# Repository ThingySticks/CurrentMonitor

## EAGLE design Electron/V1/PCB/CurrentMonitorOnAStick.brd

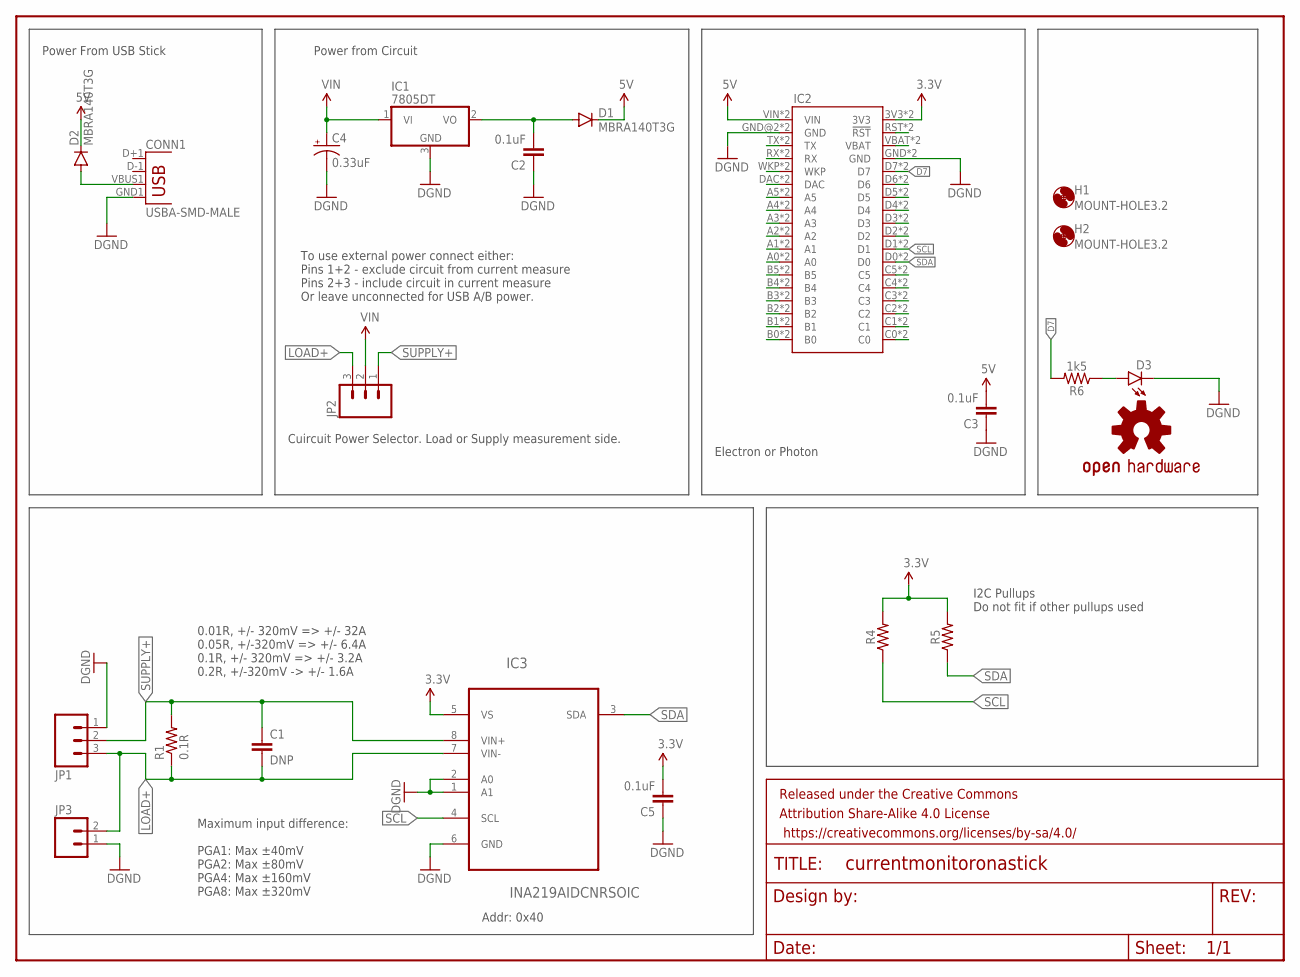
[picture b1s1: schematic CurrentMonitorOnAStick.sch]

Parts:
C1: DNP; 0805
C2, C3, C5: 0.1uF; 0805
C4: 0.33uF; EIA3216
CONN1: USBA-SMD-MALE; USB-A-SMT-MALE
D1, D2: MBRA140T3G; SMA-DIODE
D3: LED1206-BOTTOM; LED-1206-BOTTOM
FRAME2: FRAME-LETTER; CREATIVE_COMMONS
H1, H2: MOUNT-HOLE3.2; 3,2
IC1: 7805DT; TO252
IC2: ELECTRONDUALNAMED; ELECTRON_SIMPLE_SILK_NAMES_DUAL
IC3: INA219AIDCNRSOIC; SO08
JP1: M03-SCREW-5MM; SCREWTERMINAL-5MM-3
JP2: M03PTH; 1X03
JP3: M025MM; SCREWTERMINAL-5MM-2
LOGO1: OSHW-LOGOM; OSHW-LOGO-M
R1: 0.1R; 2512
R4, R5: 0805
R6: 1k5; 0805

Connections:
3.3V: C5.2, IC2.3V3, IC2.3V3_1 (3V3), IC3.5 (VS), R4.2, R5.2
5V: C3.2, D1.C, D2.C, IC2.VIN, IC2.VIN_1B (VIN)
D7: IC2.D7, IC2.D7_1 (D7), R6.2
GND: C2.1, C3.1, C4.C (-), C5.1, CONN1.GND1 (GND), D3.C, IC1.3 (GND), IC2.GND, IC2.GND@2 (GND), IC2.GND_1 (GND), IC2.GND_1B (GND), IC3.1 (A1), IC3.2 (A0), IC3.6 (GND), JP1.1, JP3.1
LOAD+: C1.2, IC3.7 (VIN-), JP1.3, JP2.3, JP3.2, R1.1
unnamed: CONN1.VBUS1 (VBUS), D2.A
unnamed: C2.2, D1.A, IC1.2 (VO)
unnamed: IC2.VBAT, IC2.VBATT_1 (VBAT)
unnamed: IC2.RST (!RST), IC2.RST_1 (!RST)
unnamed: D3.A, R6.1
unnamed: IC2.D6, IC2.D6_1 (D6)
unnamed: IC2.D5, IC2.D5_1 (D5)
unnamed: IC2.D4, IC2.D4_1 (D4)
unnamed: IC2.D3, IC2.D3_1 (D3)
unnamed: IC2.D2, IC2.D2_1 (D2)
unnamed: IC2.C5, IC2.C5_1 (C5)
unnamed: IC2.C4, IC2.C4_1 (C4)
unnamed: IC2.C3, IC2.C3_1 (C3)
unnamed: IC2.C2, IC2.C2_1 (C2)
unnamed: IC2.C1, IC2.C1_1 (C1)
unnamed: IC2.C0, IC2.C0_1 (C0)
unnamed: IC2.B0, IC2.B0_1 (B0)
unnamed: IC2.B1, IC2.B1_1 (B1)
unnamed: IC2.B2, IC2.B2_1 (B2)
unnamed: IC2.B3, IC2.B3_1 (B3)
unnamed: IC2.B4, IC2.B4_1 (B4)
unnamed: IC2.B5, IC2.B5_1 (B5)
unnamed: IC2.A0, IC2.A0_1 (A0)
unnamed: IC2.A1, IC2.A1_1 (A1)
unnamed: IC2.A2, IC2.A2_1 (A2)
unnamed: IC2.A3, IC2.A3_1 (A3)
unnamed: IC2.A4, IC2.A4_1 (A4)
unnamed: IC2.A5, IC2.A5_1 (A5)
unnamed: IC2.DAC, IC2.DAC_1 (DAC)
unnamed: IC2.WKP, IC2.WKP_1 (WKP)
unnamed: IC2.RX, IC2.RX_1 (RX)
unnamed: IC2.TX, IC2.TX_1 (TX)
SCL: IC2.D1, IC2.D1_1 (D1), IC3.4 (SCL), R4.1
SDA: IC2.D0, IC2.D0_1 (D0), IC3.3 (SDA), R5.1
SUPPLY+: C1.1, IC3.8 (VIN+), JP1.2, JP2.1, R1.2
VIN: C4.A (+), IC1.1 (VI), JP2.2

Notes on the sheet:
To use external power connect either: Pins 1+2 - exclude circuit from current measure Pins 2+3 - include circuit in current measure Or leave unconnected for USB A/B power.
I2C Pullups Do not fit if other pullups used
Maximum input difference: PGA1: Max ±40mV PGA2: Max ±80mV PGA4: Max ±160mV PGA8: Max ±320mV
0.01R, +/- 320mV => +/- 32A 0.05R, +/-320mV => +/- 6.4A 0.1R, +/- 320mV => +/- 3.2A 0.2R, +/-320mV -> +/- 1.6A
Power from Circuit
Power From USB Stick
Cuircuit Power Selector. Load or Supply measurement side.
Electron or Photon
Addr: 0x40

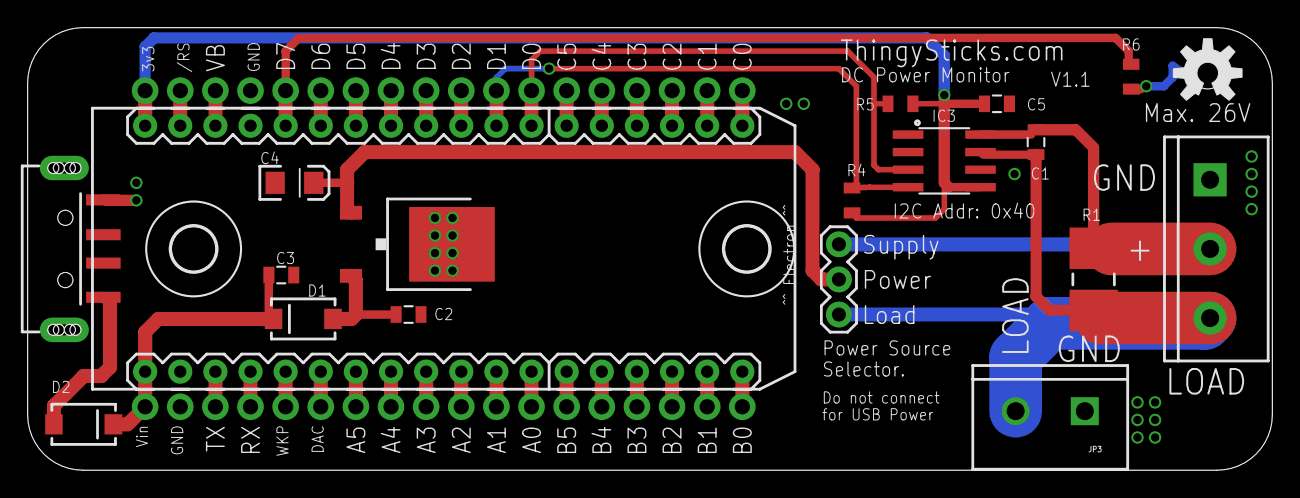
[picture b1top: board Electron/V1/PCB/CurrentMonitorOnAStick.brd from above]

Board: 2 copper layers, 90.0 x 32.0 mm, 23 parts (1 on the bottom side), 41 nets.

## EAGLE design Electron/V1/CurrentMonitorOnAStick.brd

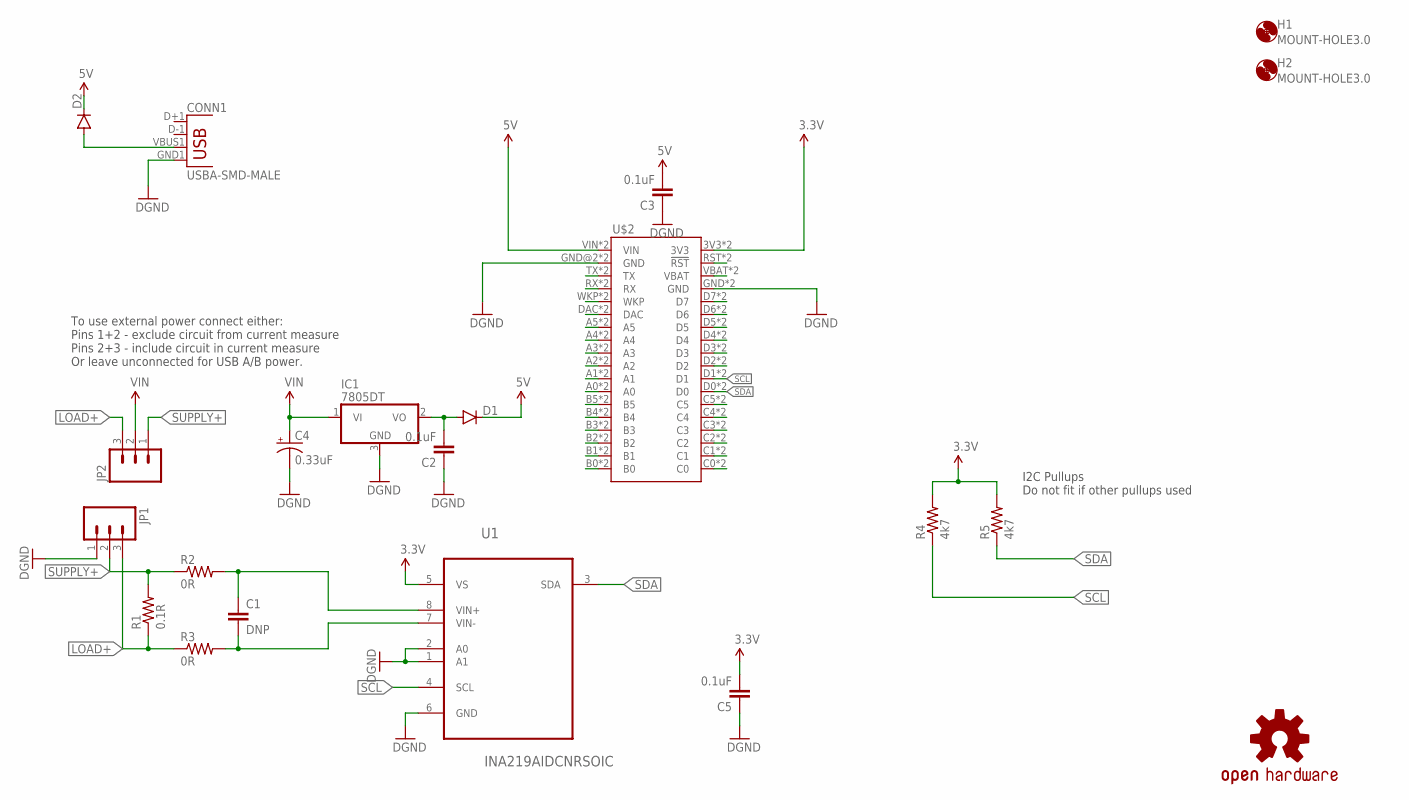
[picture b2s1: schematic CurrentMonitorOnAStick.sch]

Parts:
C1: DNP; 0805
C2, C3, C5: 0.1uF; 0805
C4: 0.33uF; EIA3216
CONN1: USBA-SMD-MALE; USB-A-SMT-MALE
D1, D2: DIODESMA; SMA-DIODE
H1, H2: MOUNT-HOLE3.0; 3,0
IC1: 7805DT; TO252
JP1: M03-SCREW-5MM; SCREWTERMINAL-5MM-3
JP2: M03PTH; 1X03
LOGO2: OSHW-LOGOS; OSHW-LOGO-S
R1: 0.1R; 2512
R2, R3: 0R; 0805
R4, R5: 4k7; 0805
U1: INA219AIDCNRSOIC; SO08
U$2: ELECTRONDUALNAMED; ELECTRON_SIMPLE_SILK_NAMES_DUAL

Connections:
3.3V: C5.2, R4.2, R5.2, U1.5 (VS), U$2.3V3, U$2.3V3_1 (3V3)
5V: C3.2, D1.C, D2.C, U$2.VIN, U$2.VIN_1B (VIN)
GND: C2.1, C3.1, C4.C (-), C5.1, CONN1.GND1 (GND), IC1.3 (GND), JP1.1, U1.1 (A1), U1.2 (A0), U1.6 (GND), U$2.GND, U$2.GND@2 (GND), U$2.GND_1 (GND), U$2.GND_1B (GND)
LOAD+: JP1.3, JP2.3, R1.1, R3.1
unnamed: CONN1.VBUS1 (VBUS), D2.A
unnamed: C2.2, D1.A, IC1.2 (VO)
unnamed: C1.1, R2.2, U1.8 (VIN+)
unnamed: U$2.VBAT, U$2.VBATT_1 (VBAT)
unnamed: U$2.RST (!RST), U$2.RST_1 (!RST)
unnamed: U$2.D7, U$2.D7_1 (D7)
unnamed: C1.2, R3.2, U1.7 (VIN-)
unnamed: U$2.D6, U$2.D6_1 (D6)
unnamed: U$2.D5, U$2.D5_1 (D5)
unnamed: U$2.D4, U$2.D4_1 (D4)
unnamed: U$2.D3, U$2.D3_1 (D3)
unnamed: U$2.D2, U$2.D2_1 (D2)
unnamed: U$2.C5, U$2.C5_1 (C5)
unnamed: U$2.C4, U$2.C4_1 (C4)
unnamed: U$2.C3, U$2.C3_1 (C3)
unnamed: U$2.C2, U$2.C2_1 (C2)
unnamed: U$2.C1, U$2.C1_1 (C1)
unnamed: U$2.C0, U$2.C0_1 (C0)
unnamed: U$2.B0, U$2.B0_1 (B0)
unnamed: U$2.B1, U$2.B1_1 (B1)
unnamed: U$2.B2, U$2.B2_1 (B2)
unnamed: U$2.B3, U$2.B3_1 (B3)
unnamed: U$2.B4, U$2.B4_1 (B4)
unnamed: U$2.B5, U$2.B5_1 (B5)
unnamed: U$2.A0, U$2.A0_1 (A0)
unnamed: U$2.A1, U$2.A1_1 (A1)
unnamed: U$2.A2, U$2.A2_1 (A2)
unnamed: U$2.A3, U$2.A3_1 (A3)
unnamed: U$2.A4, U$2.A4_1 (A4)
unnamed: U$2.A5, U$2.A5_1 (A5)
unnamed: U$2.DAC, U$2.DAC_1 (DAC)
unnamed: U$2.WKP, U$2.WKP_1 (WKP)
unnamed: U$2.RX, U$2.RX_1 (RX)
unnamed: U$2.TX, U$2.TX_1 (TX)
SCL: R4.1, U1.4 (SCL), U$2.D1, U$2.D1_1 (D1)
SDA: R5.1, U1.3 (SDA), U$2.D0, U$2.D0_1 (D0)
SUPPLY+: JP1.2, JP2.1, R1.2, R2.1
VIN: C4.A (+), IC1.1 (VI), JP2.2

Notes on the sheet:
To use external power connect either: Pins 1+2 - exclude circuit from current measure Pins 2+3 - include circuit in current measure Or leave unconnected for USB A/B power.
I2C Pullups Do not fit if other pullups used

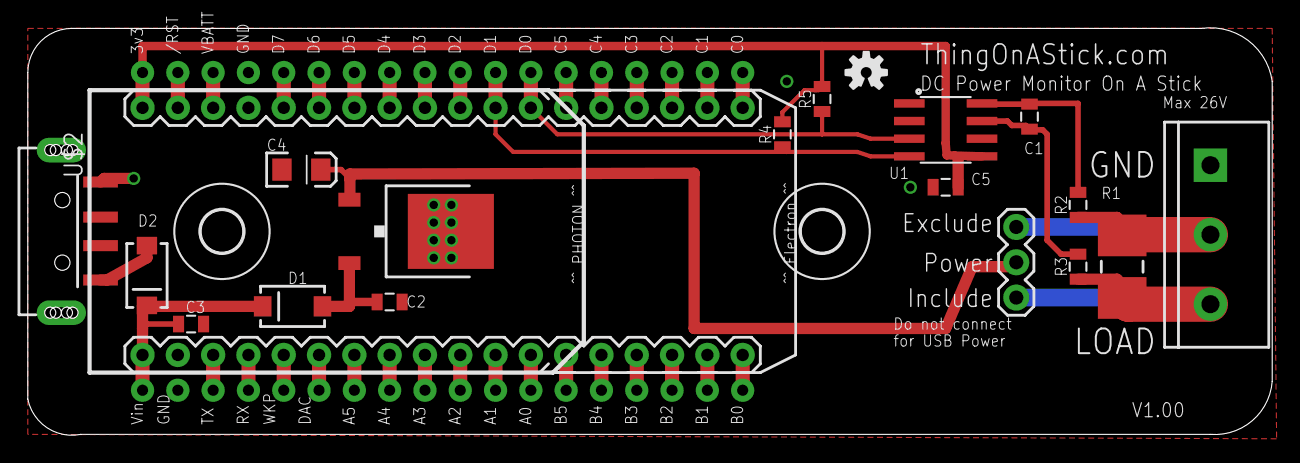
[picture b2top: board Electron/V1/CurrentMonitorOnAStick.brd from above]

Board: 2 copper layers, 89.5 x 29.3 mm, 21 parts (0 on the bottom side), 42 nets.

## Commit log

2016-02-05 Initial version (1.00) as sent to OSH Park
2016-02-05 Added gitignore
2016-03-29 Moved pcb files to PCB subfolder.
    Added datasheets
2017-08-10 Bumped to V1.1
    Added second connector to allow input and output connectors to be different whilst still allowing the single connector.
    Moved the mounting holes around a little.
    Metricified it so dimensions and mounting holes work nicely in mm.
    Added reverse mount OSH LED.

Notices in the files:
parts and their libraries:
SparkFun-Connectors: Licensing: Creative Commons ShareAlike 4.0 International - https://creativecommons.org/licenses/by-sa/4.0
SparkFun-Aesthetics: Released under the Creative Commons Attribution Share-Alike 4.0 License
SparkFun-Aesthetics: https://creativecommons.org/licenses/by-sa/4.0
